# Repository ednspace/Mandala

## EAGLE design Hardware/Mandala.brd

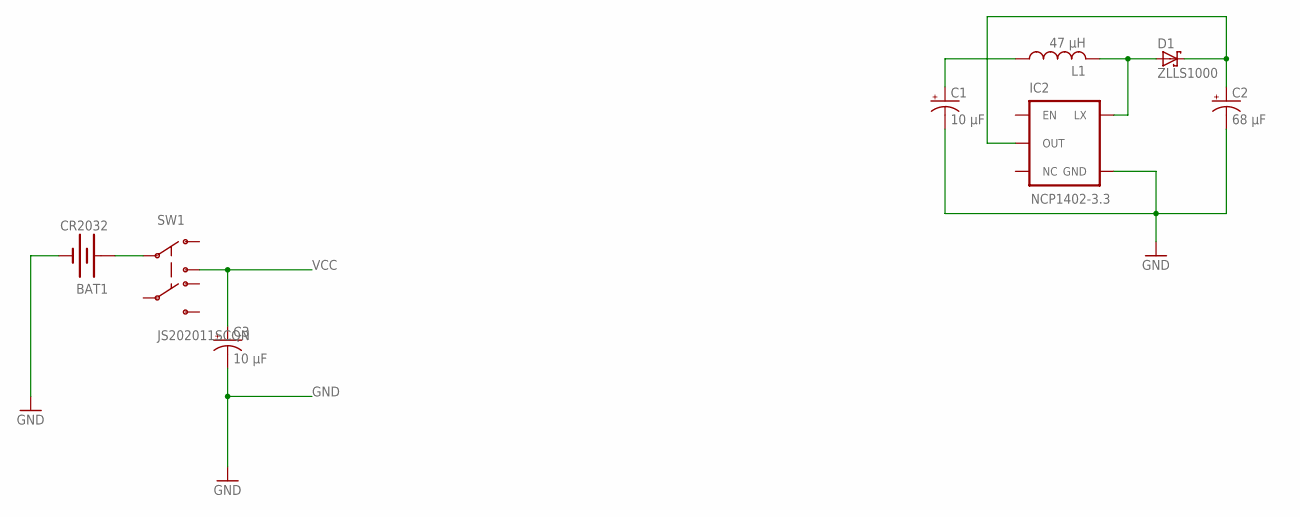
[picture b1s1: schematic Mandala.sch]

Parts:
BAT1: CR2032; BATTCON_20MM
C1, C3: 10 µF; SMC_B
C2: 68 µF; SMC_B
D1: ZLLS1000; SOT23
IC2: NCP1402-3.3; SOT23-5
L1: 47 µH; ELL5PS_INDUCTOR
SW1: JS202011SCQN; JS202011SCQN_DPDT

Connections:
GND: BAT1.2 (-), C1.-, C2.-, C3.-, IC2.4 (GND)
unnamed: D1.1 (A), IC2.5 (LX), L1.P$2 (2)
unnamed: BAT1.3 (+), SW1.P$2 (2)
VCC: C1.+, C3.+, L1.P$1 (1), SW1.P$3 (3)
VLED: C2.+, D1.3 (C), IC2.2 (OUT)

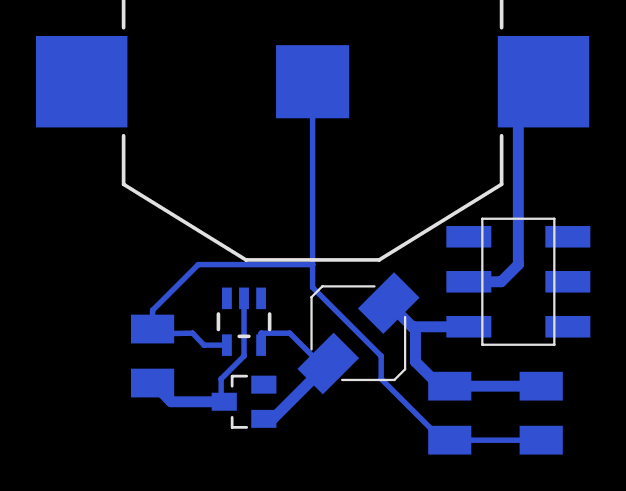
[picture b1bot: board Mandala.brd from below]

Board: 2 copper layers, 8 parts (8 on the bottom side), 5 nets.

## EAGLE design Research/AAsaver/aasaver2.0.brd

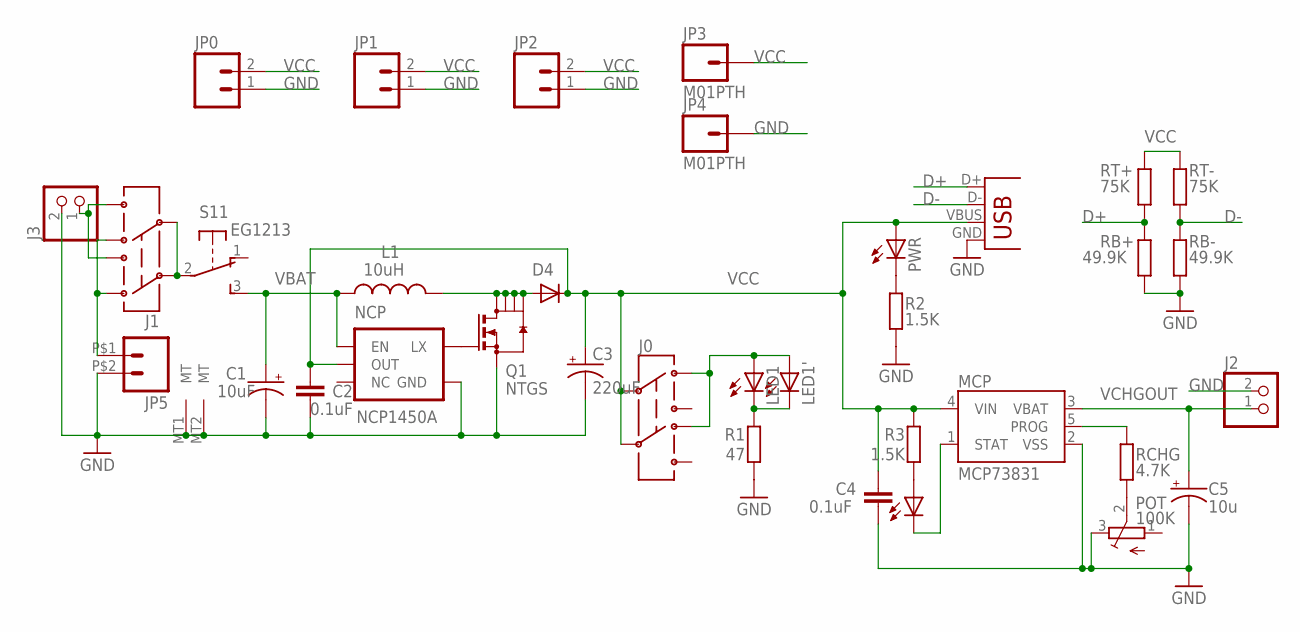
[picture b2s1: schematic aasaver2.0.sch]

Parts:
C1: 10uF; EIA3216
C2, C4: 0.1uF; C0805
C3: 220uF; EIA7343
C5: 10u; EIA3216
D4: DIODEDO216; DO216AA-DIODE
J0, J1: AYZ0202
J2, J3: JST_2PIN-SMT-RA; JST-PH-2-SMT-RA
JP0, JP1, JP2: M021X02_NO_SILK; 1X02_NO_SILK
JP3, JP4: M01PTH; 1X01
JP5: M02PTH2; 1X02_BIG
L1: 10uH; CR75
LED1, LED1': LED3MM
LED3: green; CHIPLED_0805
MCP: MCP73831; SOT23-5
NCP: NCP1450A; SOT23-5
POT: 100K; TC33X
PWR: red; CHIPLED_0805
Q1: NTGS; SOT236
R1: 47; R0805
R2, R3: 1.5K; R0805
RB+: 49.9K; R0805
RB-: 49.9K; R0805
RCHG: 4.7K; R0805
RT+: 75K; R0805
RT-: 75K; R0805
S1: EG1213
X1: USB-A-S-FEMALE

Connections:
D+: RB+.2, RT+.1, X1.D+
D-: RB-.2, RT-.1, X1.D-
GND: C1.C (-), C2.1, C3.C (-), C4.2, C5.C (-), J2.2 (1), J3.2 (1), JP0.1, JP1.1, JP2.1, JP4.1, JP5.P$2 (2), MCP.2 (VSS), NCP.4 (GND), POT.3 (E), Q1.4 (S), R1.1, R2.1, RB+.1, RB-.1, S1.MT1 (MT), S1.MT2 (MT), X1.GND
unnamed: NCP.5 (LX), Q1.3 (G)
unnamed: D4.A, L1.P$2 (2), Q1.1 (D), Q1.2 (D1), Q1.5 (D2), Q1.6 (D3)
unnamed: J1.2, J1.5, S1.2
unnamed: LED1.K (C), LED1'.K (C), R1.2
unnamed: LED3.A, R3.1
unnamed: J1.3 (1), J1.6 (4), JP5.P$1 (1)
unnamed: POT.2 (S), RCHG.1
unnamed: PWR.C, R2.2
unnamed: LED3.C, MCP.1 (STAT)
unnamed: MCP.5 (PROG), RCHG.2
unnamed: J1.1 (3), J1.4 (6), J3.1 (2)
unnamed: J0.3 (1), J0.6 (4), LED1.A, LED1'.A
VBAT: C1.A (+), L1.P$1 (1), NCP.1 (EN), S1.3 (S)
VCC: C2.2, C3.A (+), C4.1, D4.C, J0.2, J0.5, JP0.2, JP1.2, JP2.2, JP3.1, MCP.4 (VIN), NCP.2 (OUT), PWR.A, R3.2, RT+.2, RT-.2, X1.VBUS
VCHGOUT: C5.A (+), J2.1 (2), MCP.3 (VBAT)

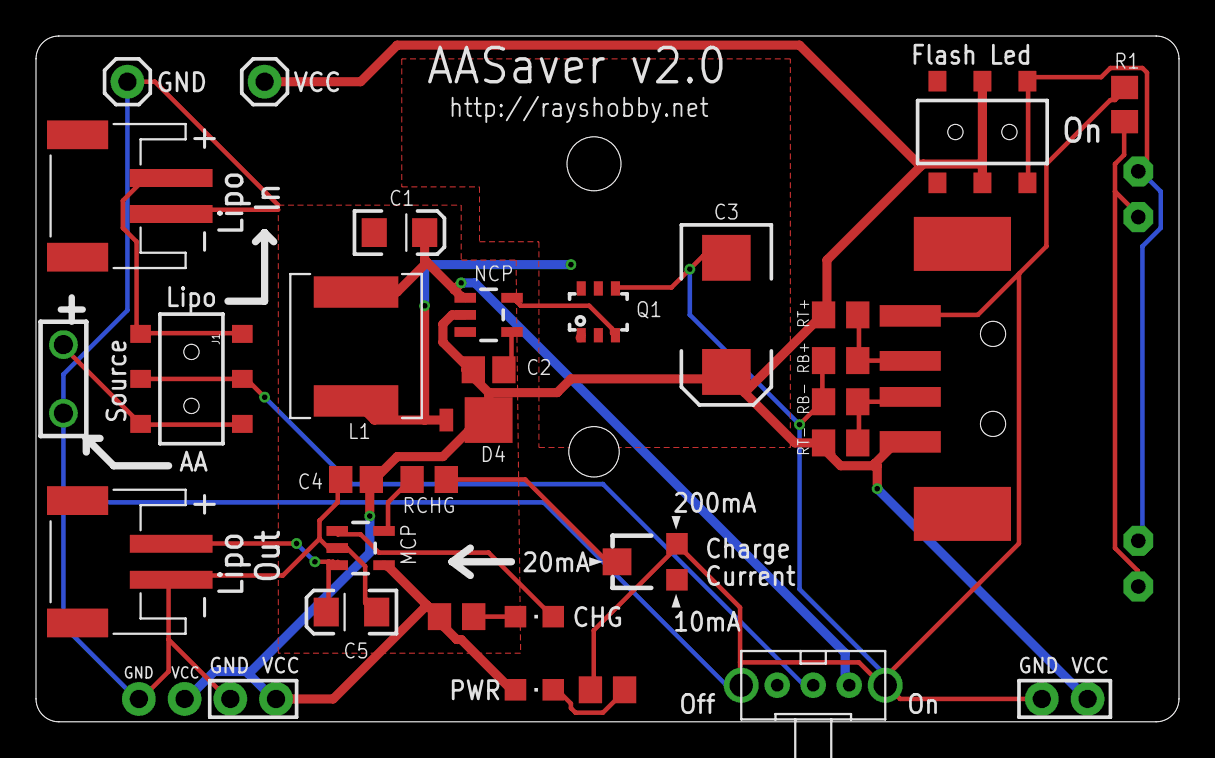
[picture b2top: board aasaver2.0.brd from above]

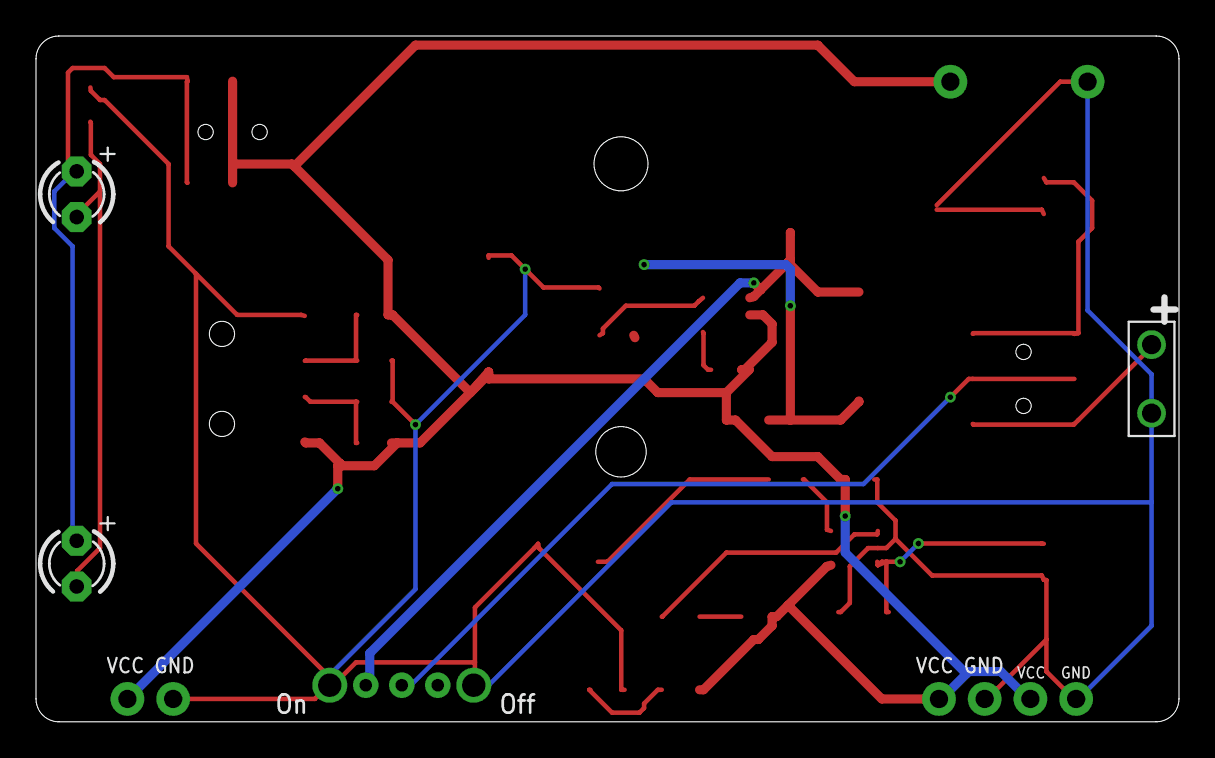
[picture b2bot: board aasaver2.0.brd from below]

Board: 2 copper layers, 63.5 x 38.1 mm, 35 parts (3 on the bottom side), 18 nets.

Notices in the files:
parts and their libraries:
SparkFunNew: Licensing: CC v3.0 Share-Alike You are welcome to use this library for commercial purposes.
